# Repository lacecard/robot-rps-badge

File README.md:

# robot-rps-badge
Official competition board design for n7jti's Robot Roshambo project

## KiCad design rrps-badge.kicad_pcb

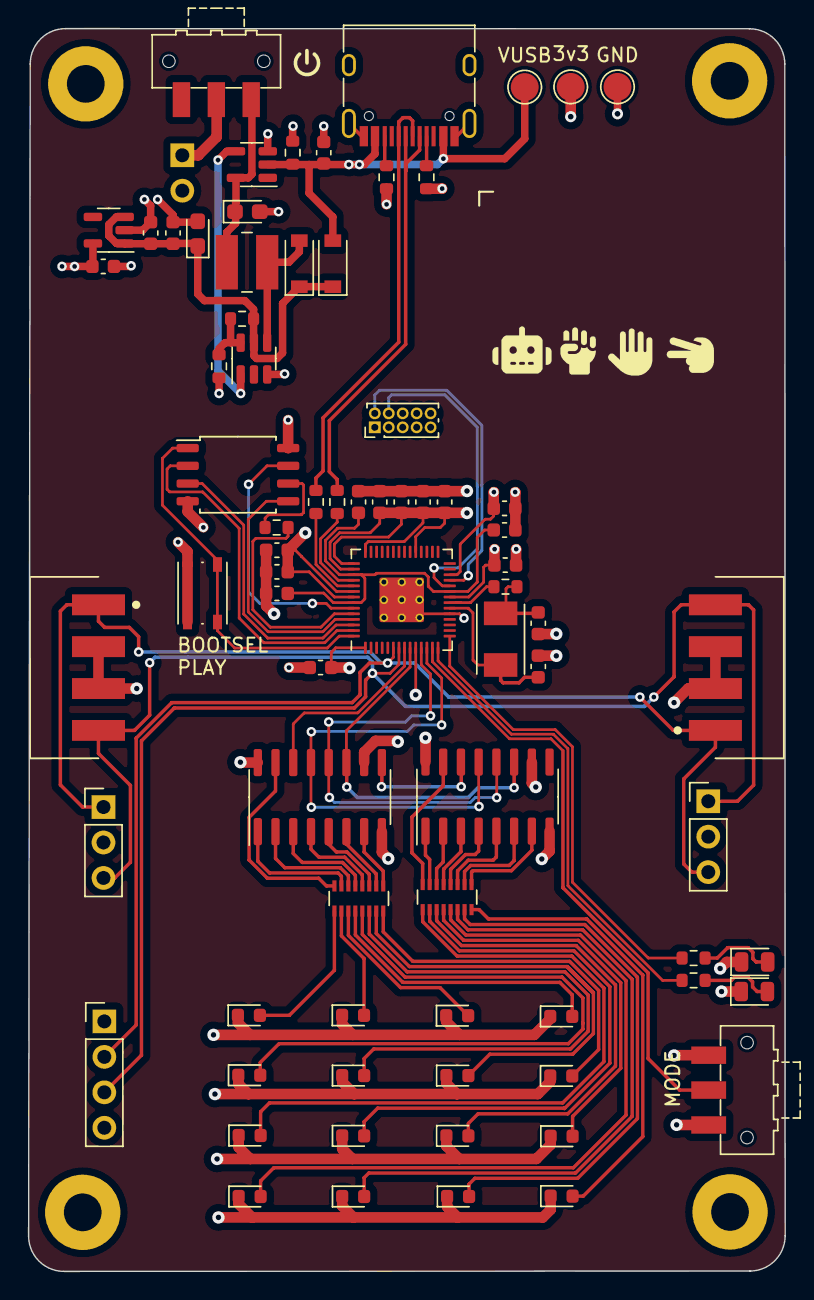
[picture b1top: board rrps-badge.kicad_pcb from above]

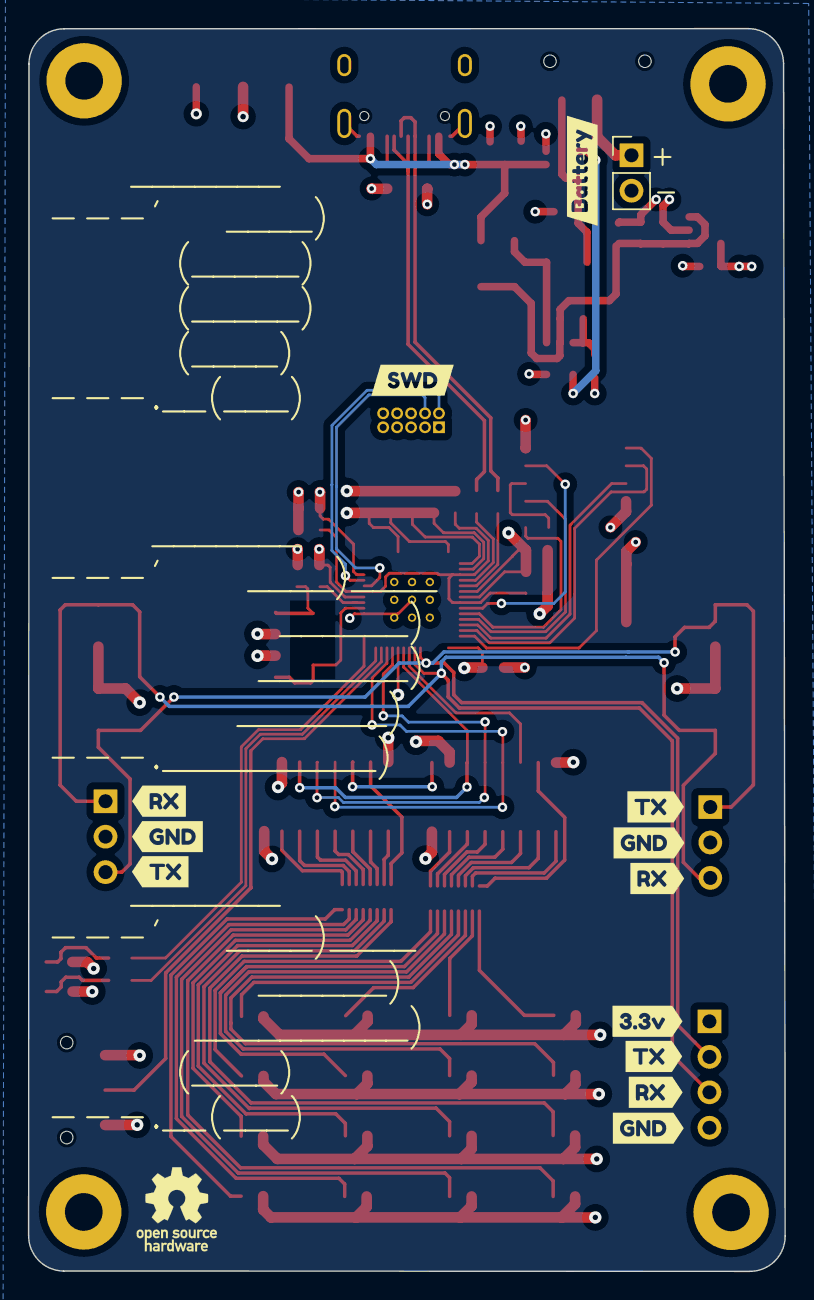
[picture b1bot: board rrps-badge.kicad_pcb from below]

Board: 4 copper layers, 54.2 x 89.0 mm, 88 parts (13 on the bottom side), 72 nets.

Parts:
3v3: TestPoint_Pad_D2.0mm
C1, C4, C5, C7, C9, C10, C11, C12, C13, C14: 100nF; C_0603_1608Metric
C2, C3: 27pF; C_0603_1608Metric
C6, C8, C16, C17, C19: 1uF; C_0603_1608Metric
C15, C18: 10uF; CP_EIA-2012-12_Kemet-R
C20: 10uF; C_0603_1608Metric
D1, D2: K1N5819HW-7-F; D_SOD-123
D3, D4, D5, D6, D7, D8, D9, D10, D11, D12, D13, D14, D15, D16, D17, D18: LED_Small; LED_0603_1608Metric
D19: Arena; LED_0805_2012Metric
D20: Player; LED_0805_2012Metric
GND: TestPoint_Pad_D2.0mm
J1: USB_C_Receptacle_USB2.0; USB_C_Receptacle_HRO_TYPE-C-31-M-12
J2: Battery (2xAA); PinHeader_1x02_P2.54mm_Vertical
J3: GameIn Debug; PinHeader_1x03_P2.54mm_Vertical
J4: GameOut Debug; PinHeader_1x03_P2.54mm_Vertical
J5: Game UART Debug; PinHeader_1x04_P2.54mm_Vertical
J6, J7: 1971567-2; TE_1971567-2
J9: Conn_02x05_Odd_Even; PinHeader_2x05_P1.00mm_Vertical
L1: VLCF4020T-100MR85
R1: 0; R_0603_1608Metric
R2: 1k; R_0603_1608Metric
R3, R4: 27; R_0603_1608Metric
R5: 2.2k; R_0603_1608Metric
R6: 3.01M; R_0603_1608Metric
R7: 1M; R_0603_1608Metric
R8, R9: 5.1k; R_0603_1608Metric
R10, R11: 220; R_0603_1608Metric
RN1, RN2: 742C163221JP; R_Array_Convex_8x0602
SW1: Power Switch; SW_SPDT_CK-JS102011SAQN
SW2: MODE_SEL; SW_SPDT_CK-JS102011SAQN
SW3: BOOTSEL; SW_Push_1P1T_NO_Vertical_Wuerth_434133025816
U1: W25Q128JVS; SOIC-8_5.23x5.23mm_P1.27mm
U2: RP2040; RP2040-QFN-56
U3: LN2266; SOT-23-6
U4: SN74AHC1G04DBVR; SOT-23-5
U5: PJ9193M33SE; SOT-23-5
U6, U7: 74HC595; SOIC-16_3.9x9.9mm_P1.27mm
VUSB: VUSB; TestPoint_Pad_D2.0mm
Y1: Crystal; Crystal_SMD_TXC_7A-2Pin_5x3.2mm
kibuzzard-650A07A5, kibuzzard-650A07A5#2: G***; kibuzzard-650A07A5
kibuzzard-650A07F7, kibuzzard-650A07F7#2: G***; kibuzzard-650A07F7
kibuzzard-650A73ED: G***; kibuzzard-650A73ED
kibuzzard-650A082B: G***; kibuzzard-650A082B
kibuzzard-650A096D: G***; kibuzzard-650A096D
kibuzzard-650A097D: G***; kibuzzard-650A097D
kibuzzard-650A0865, kibuzzard-650A0865#2: G***; kibuzzard-650A0865
kibuzzard-650A0992: G***; kibuzzard-650A0992
kibuzzard-65131468: G***; kibuzzard-65131468

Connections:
+1V1: C4.1, C5.1, C6.1, U2.23 (DVDD), U2.45 (VREG_VOUT), U2.50 (DVDD)
+3V3: 3v3.1, C1.1, C7.1, C8.1, C9.1, C10.1, C11.1, C12.1, C13.1, C14.1, C19.1, J5.1, SW2.1 (A), U1.8 (VCC), U2.1 (IOVDD), U2.10 (IOVDD), U2.22 (IOVDD), U2.26 (RUN), U2.33 (IOVDD), U2.42 (IOVDD), U2.43 (ADC_AVDD), U2.44 (VREG_IN), U2.48 (USB_VDD), U2.49 (IOVDD), U5.5 (VOUT), U6.10 (~SRCLR), U6.16 (VCC), U7.10 (~SRCLR), U7.16 (VCC)
+5V: C16.1, C17.1, C18.1, D1.1 (K), D2.1 (K), R6.1, U3.5 (VCC), U5.1 (VIN), U5.3 (EN)
/Connectors/Game_Mode: SW2.2 (B), U2.13 (GPIO10)
/Connectors/SWCLK: J9.4, U2.24 (SWCLK)
/Connectors/SWDIO: J9.2, U2.25 (SWD)
/MCU/Game_Indicator_A: R10.2, U2.15 (GPIO12)
/MCU/Game_Indicator_P: R11.2, U2.14 (GPIO11)
/MCU/LED_CLK: U2.9 (GPIO7), U6.11 (SRCLK), U7.11 (SRCLK)
/MCU/LED_DATA: U2.8 (GPIO6), U6.14 (SER)
/MCU/LED_LATCH: U2.11 (GPIO8), U6.12 (RCLK), U7.12 (RCLK)
/MCU/LED_OE: U2.12 (GPIO9), U6.13 (~OE), U7.13 (~OE)
/MCU/USB_D+: J1.A6 (D+), J1.B6 (D+), R3.1
/MCU/USB_D-: J1.A7 (D-), J1.B7 (D-), R4.1
BOOST: U3.1 (CE), U4.4 (Y)
Flash_Sel: SW3.2 (B), U1.1 (~CS), U2.56 (QSPI_SS)
GAME_RX: J3.3, J4.1, J5.3, J6.4, J7.4, U2.7 (GPIO5)
GAME_TX: J3.1, J4.3, J5.2, J6.1, J7.1, U2.6 (GPIO4)
GND: C1.2, C2.1, C3.1, C4.2, C5.2, C6.2, C7.2, C8.2, C9.2, C10.2, C11.2, C12.2, C13.2, C14.2, C15.2, C16.2, C17.2, C18.2, C19.2, C20.2, D3.1 (K), D4.1 (K), D5.1 (K), D6.1 (K), D7.1 (K), D8.1 (K), D9.1 (K), D10.1 (K), D11.1 (K), D12.1 (K), D13.1 (K), D14.1 (K), D15.1 (K), D16.1 (K), D17.1 (K), D18.1 (K), D19.1 (K), D20.1 (K), GND.1, J1.A1 (GND), J1.A12 (GND), J1.B1 (GND), J1.B12 (GND), J1.S1 (SHIELD), J2.2, J3.2, J4.2, J5.4, J6.2, J6.3, J7.2, J7.3, J9.3, J9.5, J9.9, R5.2, R7.2, R8.2, R9.2, SW2.3 (C), SW3.1 (A), U1.4 (GND), U2.19 (TESTEN), U2.57 (GND), U3.3 (GND), U4.3 (GND), U5.2 (GND), U6.8 (GND), U7.8 (GND)
unnamed: C2.2, U2.20 (XIN), Y1.1
unnamed: C3.2, R2.1, Y1.2
unnamed: D2.2 (A), L1.1, U3.4 (LX)
unnamed: D3.2 (A), RN1.1 (R1.1)
unnamed: D4.2 (A), RN1.2 (R2.1)
unnamed: D5.2 (A), RN1.3 (R3.1)
unnamed: D6.2 (A), RN1.4 (R4.1)
unnamed: D7.2 (A), RN1.5 (R5.1)
unnamed: D8.2 (A), RN1.6 (R6.1)
unnamed: D9.2 (A), RN1.7 (R7.1)
unnamed: D10.2 (A), RN1.8 (R8.1)
unnamed: D11.2 (A), RN2.1 (R1.1)
unnamed: D12.2 (A), RN2.2 (R2.1)
unnamed: D13.2 (A), RN2.3 (R3.1)
unnamed: D14.2 (A), RN2.4 (R4.1)
unnamed: D15.2 (A), RN2.5 (R5.1)
unnamed: D16.2 (A), RN2.6 (R6.1)
unnamed: D17.2 (A), RN2.7 (R7.1)
unnamed: D18.2 (A), RN2.8 (R8.1)
unnamed: D19.2 (A), R10.1
unnamed: D20.2 (A), R11.1
unnamed: J1.A5 (CC1), R8.1
unnamed: J1.B5 (CC2), R9.1
unnamed: J2.1, SW1.2 (B)
unnamed: R1.1, U1.6 (CLK)
unnamed: R1.2, U2.52 (QSPI_SCLK)
unnamed: R2.2, U2.21 (XOUT)
unnamed: R3.2, U2.47 (USB_DP)
unnamed: R4.2, U2.46 (USB_DM)
unnamed: R6.2, R7.1, U3.6 (FB)
unnamed: RN1.9 (R8.2), U6.7 (QH)
unnamed: RN1.10 (R7.2), U6.6 (QG)
unnamed: RN1.11 (R6.2), U6.5 (QF)
unnamed: RN1.12 (R5.2), U6.4 (QE)
unnamed: RN1.13 (R4.2), U6.3 (QD)
unnamed: RN1.14 (R3.2), U6.2 (QC)
unnamed: RN1.15 (R2.2), U6.1 (QB)
unnamed: RN1.16 (R1.2), U6.15 (QA)
unnamed: RN2.9 (R8.2), U7.7 (QH)
unnamed: RN2.10 (R7.2), U7.6 (QG)
unnamed: RN2.11 (R6.2), U7.5 (QF)
unnamed: RN2.12 (R5.2), U7.4 (QE)
unnamed: RN2.13 (R4.2), U7.3 (QD)
unnamed: RN2.14 (R3.2), U7.2 (QC)
unnamed: RN2.15 (R2.2), U7.1 (QB)
unnamed: RN2.16 (R1.2), U7.15 (QA)
unnamed: U1.2 (DO(IO1)), U2.55 (QSPI_SD1)
unnamed: U1.3 (IO2), U2.54 (QSPI_SD2)
unnamed: U1.5 (DI(IO0)), U2.53 (QSPI_SD0)
unnamed: U1.7 (IO3), U2.51 (QSPI_SD3)
unnamed: U6.9 (QH'), U7.14 (SER)
VBAT: C15.1, L1.2, SW1.1 (A), U4.5 (VCC)
VUSB: C20.1, D1.2 (A), J1.A4 (VBUS), J1.A9 (VBUS), J1.B4 (VBUS), J1.B9 (VBUS), R5.1, U4.2 (A), VUSB.1

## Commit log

2023-10-22 general cleanup
2023-10-22 updated gitignore
2023-10-22 Added schematic PDF
2023-10-22 Added board renders
2023-10-22 Removed older renders
